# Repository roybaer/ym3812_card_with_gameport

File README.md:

# YM3812 card with gameport

This 8-bit ISA card is essentially a clone of Amstrad's Adlib clone with gameport.

The routing and silk screen are a bit tidier and the DA15 connector has been shifted to make it easier to adapt off-the-shelf slot brackets.

## Front view

This picture shows the front of the card.

## Vintage components

Besides readily available standard components, the card uses four vintage components:

- Yamaha YM3812 (OPL2 FM synthesizer)
- Yamaha Y3014B (matching DAC for OPL2)
- TDA7233 (amplifier)
- NE558 (quad timer IC)

## License

The following license applies to the files in this repository:

This work is licensed under the Creative Commons Attribution-ShareAlike 4.0 International License. To view a copy of this license, visit http://creativecommons.org/licenses/by-sa/4.0/ or send a letter to Creative Commons, PO Box 1866, Mountain View, CA 94042, USA.

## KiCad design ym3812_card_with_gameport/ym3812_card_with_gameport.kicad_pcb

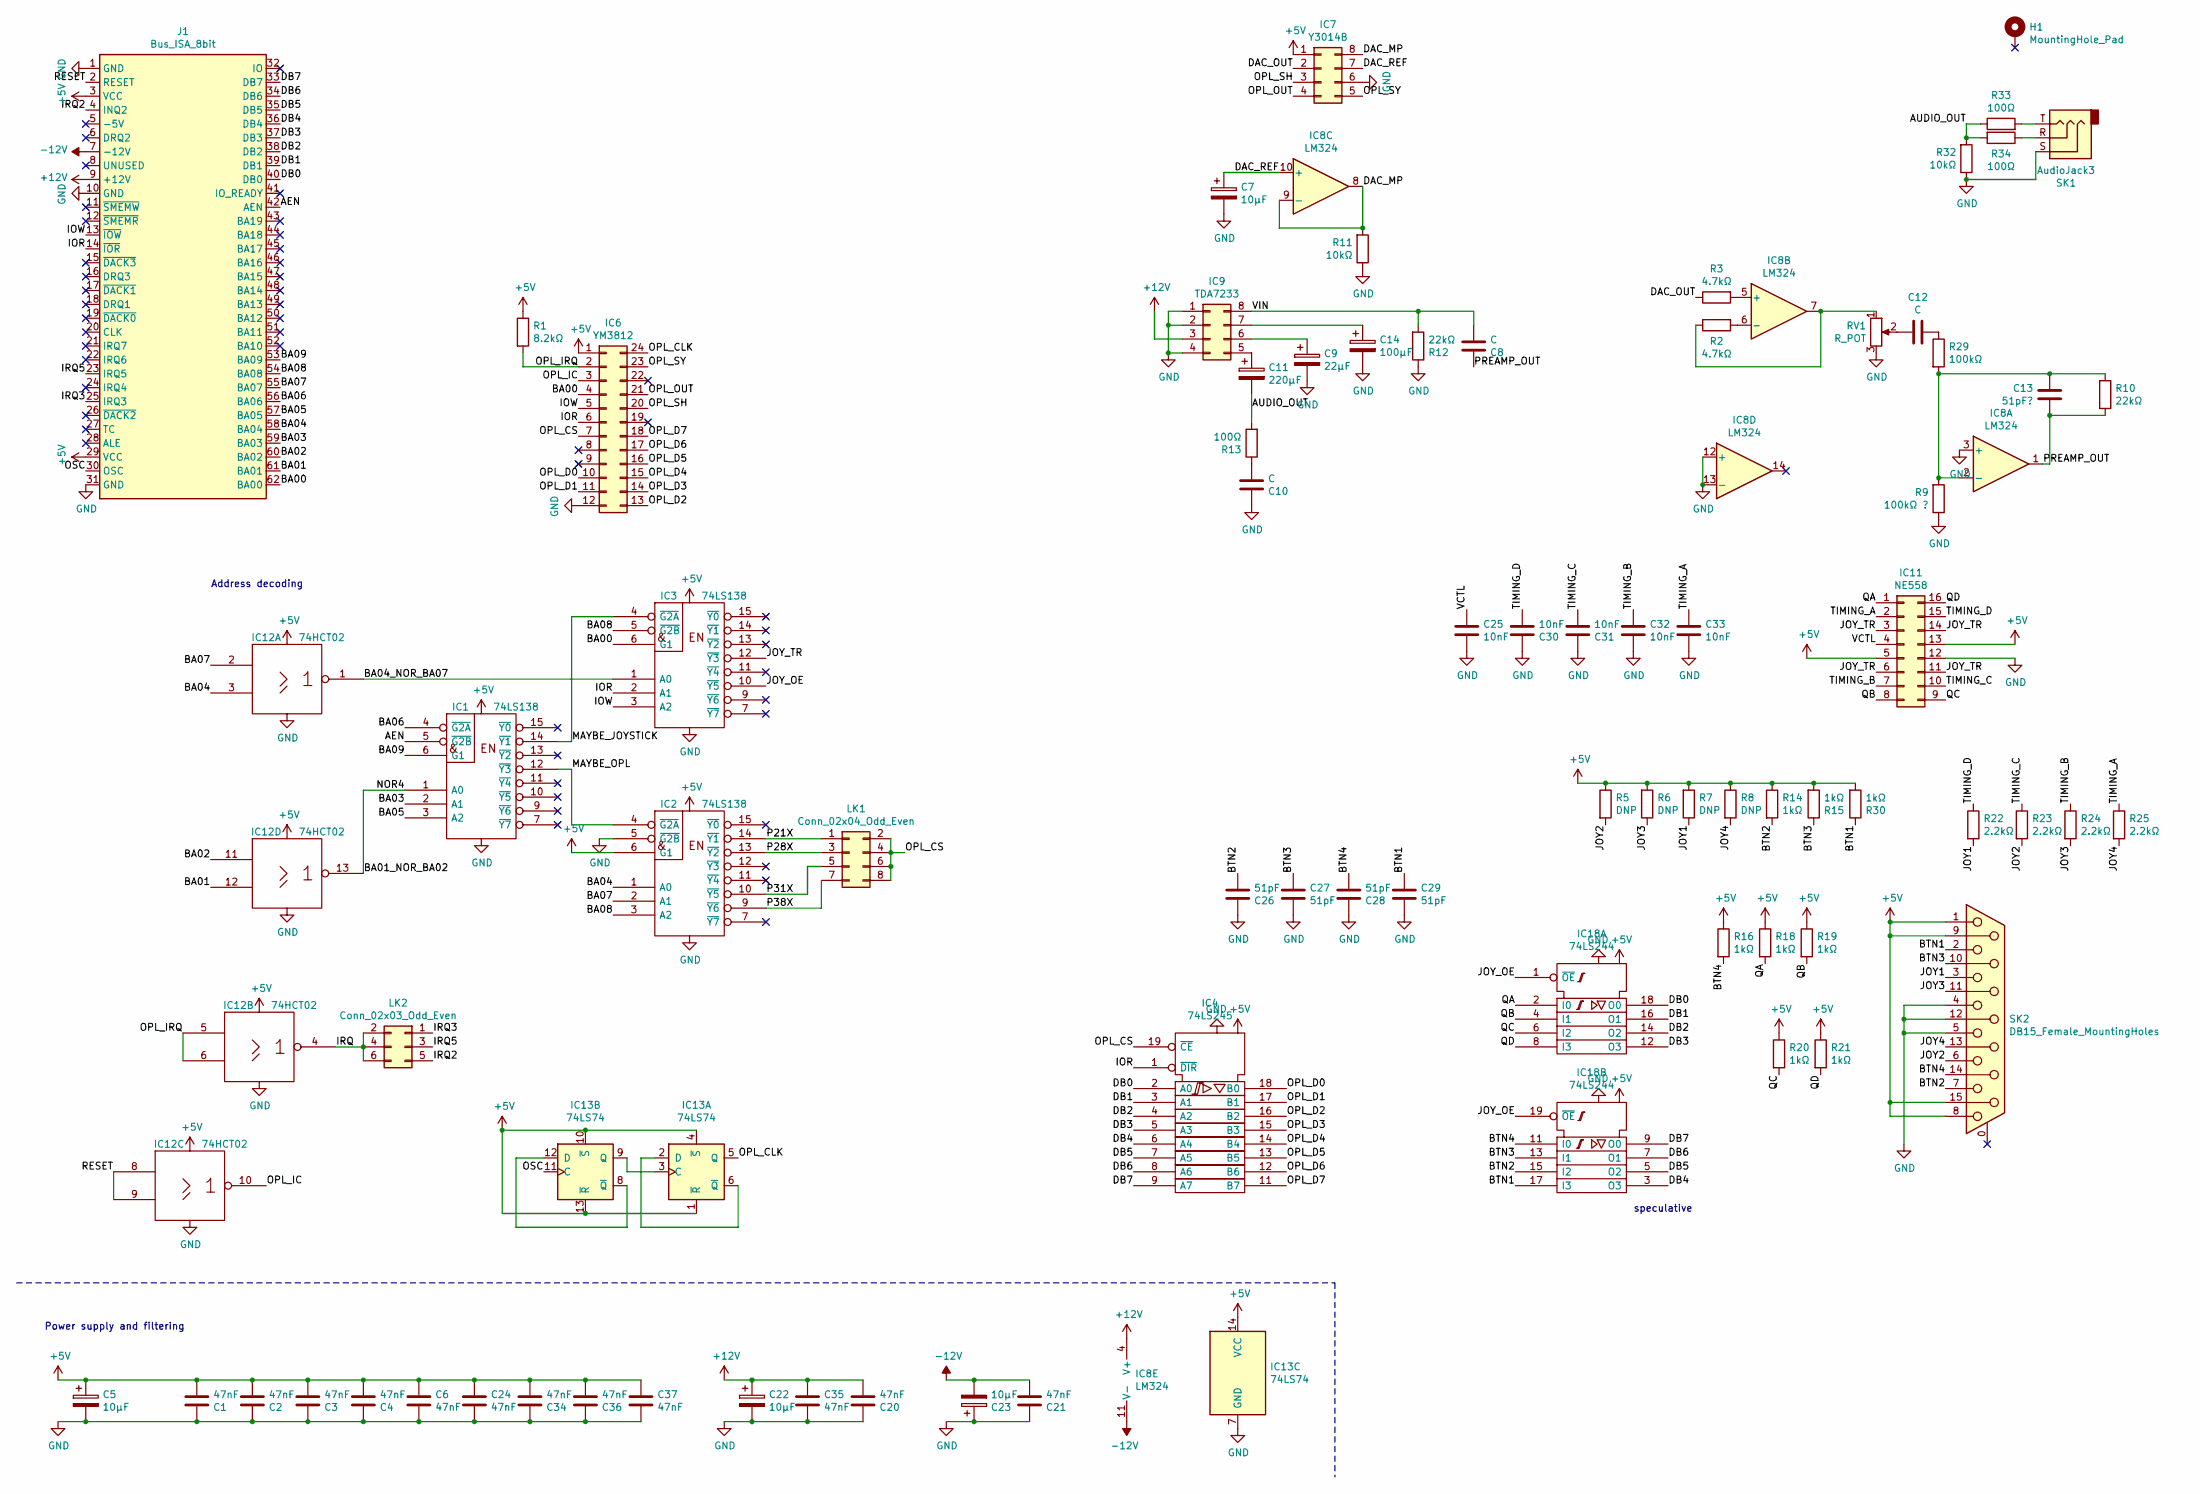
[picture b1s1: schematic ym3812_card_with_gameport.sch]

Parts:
C1, C2, C3, C4, C6, C20, C21, C24, C34, C35, C36, C37: 47nF; C_1206_3216Metric
C5, C7, C22, C23: 10µF; CP_Radial_D5.0mm_P2.50mm
C8, C10, C12: C; C_1206_3216Metric
C9: 22µF; CP_Radial_D5.0mm_P2.50mm
C11: 220µF; CP_Radial_D8.0mm_P5.00mm
C13: 51pF?; C_1206_3216Metric
C14: 100µF; CP_Radial_D6.3mm_P2.50mm
C25, C30, C31, C32, C33: 10nF; C_1206_3216Metric
C26, C27, C28, C29: 51pF; C_1206_3216Metric
H1: MountingHole_Pad; MountingHole_3.2mm_M3_Pad_Via
IC1, IC2, IC3: 74LS138; SOIC-16_3.9x9.9mm_P1.27mm
IC4: 74LS245; SOIC-20W_7.5x12.8mm_P1.27mm
IC6: YM3812; DIP-24_W15.24mm
IC7: Y3014B; DIP-8_W7.62mm
IC8: LM324; SOIC-14_3.9x8.7mm_P1.27mm
IC9: TDA7233; DIP-8_W7.62mm
IC11: NE558; SOIC-16W_7.5x10.3mm_P1.27mm
IC12: 74HCT02; SOIC-14_3.9x8.7mm_P1.27mm
IC13: 74LS74; SOIC-14_3.9x8.7mm_P1.27mm
IC18: 74LS244; SOIC-20W_7.5x12.8mm_P1.27mm
J1: Bus_ISA_8bit; BUS_AT
LK1: Conn_02x04_Odd_Even; PinHeader_2x04_P2.54mm_Vertical
LK2: Conn_02x03_Odd_Even; PinHeader_2x03_P2.54mm_Vertical
R1: 8.2kΩ; R_1206_3216Metric
R2, R3: 4.7kΩ; R_1206_3216Metric
R5, R6, R7, R8: DNP; R_1206_3216Metric
R9: 100kΩ ?; R_1206_3216Metric
R10, R12: 22kΩ; R_1206_3216Metric
R11, R32: 10kΩ; R_1206_3216Metric
R13, R33, R34: 100Ω; R_1206_3216Metric
R14, R15, R16, R18, R19, R20, R21, R30: 1kΩ; R_1206_3216Metric
R22, R23, R24, R25: 2.2kΩ; R_1206_3216Metric
R29: 100kΩ; R_1206_3216Metric
RV1: R_POT; Potentiometer_Alps_RK09K_Single_Horizontal
SK1: AudioJack3; Jack_3.5mm_CUI_SJ1-3525N_Horizontal
SK2: DB15_Female_MountingHoles; DSUB-15_Female_Horizontal_P2.77x2.84mm_EdgePinOffset7.70mm_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

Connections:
+5V: C1.2, C2.2, C3.2, C4.2, C5.1, C6.1, C24.1, C34.2, C36.2, C37.1, IC1.16 (VCC), IC2.6 (G1), IC2.16 (VCC), IC3.16 (VCC), IC4.20 (VCC), IC6.1, IC7.1, IC11.5, IC11.13, IC12.14 (VCC), IC13.1 (~R), IC13.4 (~S), IC13.10 (~S), IC13.13 (~R), IC13.14 (VCC), IC18.20 (VCC), J1.3 (VCC), J1.29 (VCC), R1.1, R5.1, R6.2, R7.2, R8.1, R14.1, R15.2, R16.1, R18.1, R19.1, R20.1, R21.1, R30.2, SK2.1, SK2.8, SK2.9, SK2.15
+12V: C20.2, C22.1, C35.1, IC8.4 (V+), IC9.3, J1.9 (+12V)
-12V: C21.2, C23.2, IC8.11 (V-), J1.7 (-12V)
/AEN: IC1.5 (~G2B), J1.42 (AEN)
/AUDIO_OUT: C11.2, R13.2, R32.2, R33.1, R34.2
/BA00: IC3.6 (G1), IC6.4, J1.62 (BA00)
/BA01: IC12.12, J1.61 (BA01)
/BA01_NOR_BA02: IC1.1 (A0), IC12.13
/BA02: IC12.11, J1.60 (BA02)
/BA03: IC1.2 (A1), J1.59 (BA03)
/BA04: IC2.1 (A0), IC12.3, J1.58 (BA04)
/BA04_NOR_BA07: IC3.1 (A0), IC12.1
/BA05: IC1.3 (A2), J1.57 (BA05)
/BA06: IC1.4 (~G2A), J1.56 (BA06)
/BA07: IC2.2 (A1), IC12.2, J1.55 (BA07)
/BA08: IC2.3 (A2), IC3.5 (~G2B), J1.54 (BA08)
/BA09: IC1.6 (G1), J1.53 (BA09)
/BTN1: C29.1, IC18.17 (I3), R30.1, SK2.2
/BTN2: C26.2, IC18.15 (I2), R14.2, SK2.7
/BTN3: C27.1, IC18.13 (I1), R15.1, SK2.10
/BTN4: C28.2, IC18.11 (I0), R16.2, SK2.14
/DAC_MP: IC7.8, IC8.8, IC8.9 (-), R11.2
/DAC_OUT: IC7.2, R3.1
/DAC_REF: C7.1, IC7.7, IC8.10 (+)
/DB0: IC4.2 (A0), IC18.18 (O0), J1.40 (DB0)
/DB1: IC4.3 (A1), IC18.16 (O1), J1.39 (DB1)
/DB2: IC4.4 (A2), IC18.14 (O2), J1.38 (DB2)
/DB3: IC4.5 (A3), IC18.12 (O3), J1.37 (DB3)
/DB4: IC4.6 (A4), IC18.3 (O3), J1.36 (DB4)
/DB5: IC4.7 (A5), IC18.5 (O2), J1.35 (DB5)
/DB6: IC4.8 (A6), IC18.7 (O1), J1.34 (DB6)
/DB7: IC4.9 (A7), IC18.9 (O0), J1.33 (DB7)
/IOR: IC3.2 (A1), IC4.1 (~DIR), IC6.6, J1.14 (~IOR)
/IOW: IC3.3 (A2), IC6.5, J1.13 (~IOW)
/IRQ: IC12.4, LK2.2, LK2.4, LK2.6
/IRQ2: J1.4 (INQ2), LK2.5
/IRQ3: J1.25 (IRQ3), LK2.1
/IRQ5: J1.23 (IRQ5), LK2.3
/JOY1: R7.1, R22.2, SK2.3
/JOY2: R5.2, R23.2, SK2.6
/JOY3: R6.1, R24.2, SK2.11 (P111)
/JOY4: R8.2, R25.2, SK2.13
/JOY_OE: IC3.10 (~Y5), IC18.1 (~OE), IC18.19 (~OE)
/JOY_TR: IC3.12 (~Y3), IC11.3, IC11.6, IC11.11, IC11.14
/MAYBE_JOYSTICK: IC1.14 (~Y1), IC3.4 (~G2A)
/MAYBE_OPL: IC1.12 (~Y3), IC2.4 (~G2A)
/OPL_CLK: IC6.24, IC13.5 (Q)
/OPL_CS: IC4.19 (~CE), IC6.7, LK1.2, LK1.4, LK1.6, LK1.8
/OPL_D0: IC4.18 (B0), IC6.10
/OPL_D1: IC4.17 (B1), IC6.11
/OPL_D2: IC4.16 (B2), IC6.13
/OPL_D3: IC4.15 (B3), IC6.14
/OPL_D4: IC4.14 (B4), IC6.15
/OPL_D5: IC4.13 (B5), IC6.16
/OPL_D6: IC4.12 (B6), IC6.17
/OPL_D7: IC4.11 (B7), IC6.18
/OPL_IC: IC6.3, IC12.10
/OPL_IRQ: IC6.2, IC12.5, IC12.6, R1.2
/OPL_OUT: IC6.21, IC7.4
/OPL_SH: IC6.20, IC7.3
/OPL_SY: IC6.23, IC7.5
/OSC: IC13.11 (C), J1.30 (OSC)
/P21X: IC2.14 (~Y1), LK1.1
/P28X: IC2.13 (~Y2), LK1.3
/P31X: IC2.10 (~Y5), LK1.5
/P38X: IC2.9 (~Y6), LK1.7
/PREAMP_OUT: C8.1, C13.1, IC8.1, R10.1
/QA: IC11.1, IC18.2 (I0), R18.2
/QB: IC11.8, IC18.4 (I1), R19.2
/QC: IC11.9, IC18.6 (I2), R20.2
/QD: IC11.16, IC18.8 (I3), R21.2
/RESET: IC12.8, IC12.9, J1.2 (RESET)
/TIMING_A: C33.1, IC11.2, R25.1
/TIMING_B: C32.1, IC11.7, R24.1
/TIMING_C: C31.2, IC11.10, R23.1
/TIMING_D: C30.2, IC11.15, R22.1
/VCTL: C25.1, IC11.4
/VIN: C8.2, IC9.8, R12.2
GND: C1.1, C2.1, C3.1, C4.1, C5.2, C6.2, C7.2, C9.2, C10.1, C14.2, C20.1, C21.1, C22.2, C23.1, C24.2, C25.2, C26.1, C27.2, C28.1, C29.2, C30.1, C31.1, C32.2, C33.2, C34.1, C35.2, C36.1, C37.2, IC1.8 (GND), IC2.5 (~G2B), IC2.8 (GND), IC3.8 (GND), IC4.10 (GND), IC6.12, IC7.6, IC8.3 (+), IC8.12 (+), IC8.13 (-), IC9.1, IC9.2, IC9.4, IC11.12, IC12.7 (GND), IC13.7 (GND), IC18.10 (GND), J1.1 (GND), J1.10 (GND), J1.31 (GND), R9.1, R11.1, R12.1, R32.1, RV1.3, SK1.S, SK2.4, SK2.5, SK2.12
unnamed: C9.1, IC9.6
unnamed: C10.2, R13.1
unnamed: C11.1, IC9.5
unnamed: C12.1, RV1.2
unnamed: C12.2, R29.1
unnamed: C13.2, IC8.2 (-), R9.2, R10.2, R29.2
unnamed: C14.1, IC9.7
unnamed: IC8.5 (+), R3.2
unnamed: IC8.6 (-), R2.2
unnamed: IC8.7, R2.1, RV1.1
unnamed: IC13.2 (D), IC13.6 (~Q)
unnamed: IC13.3 (C), IC13.9 (Q)
unnamed: IC13.8 (~Q), IC13.12 (D)
unnamed: R33.2, SK1.T
unnamed: R34.1, SK1.R

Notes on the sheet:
speculative
Power supply and filtering
Address decoding

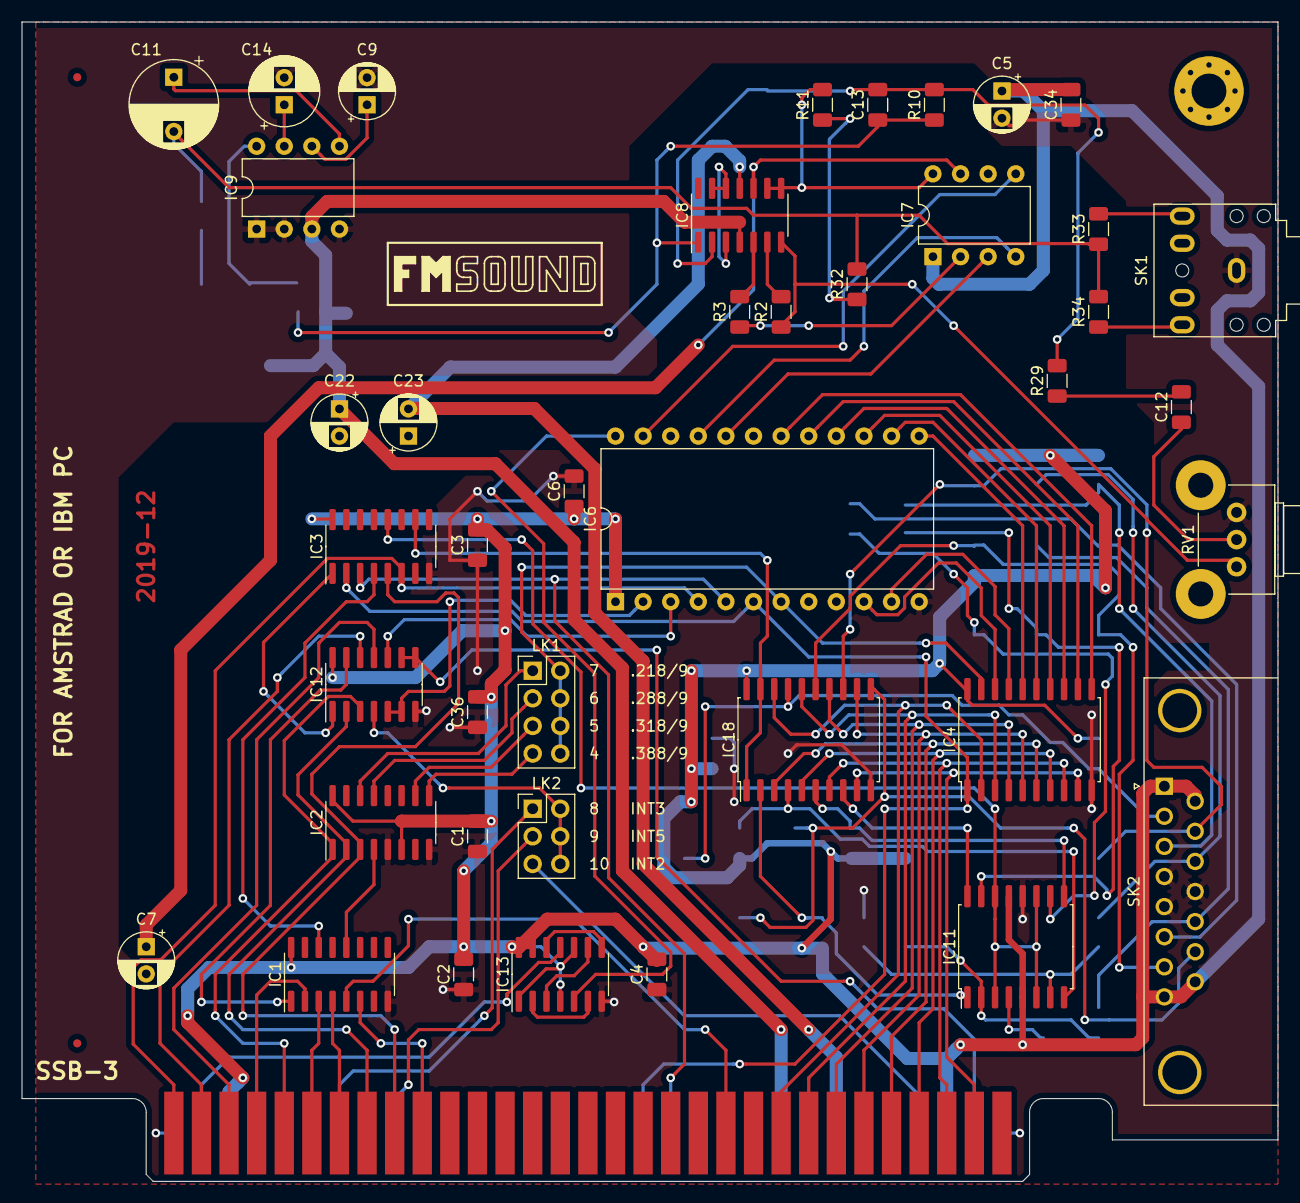
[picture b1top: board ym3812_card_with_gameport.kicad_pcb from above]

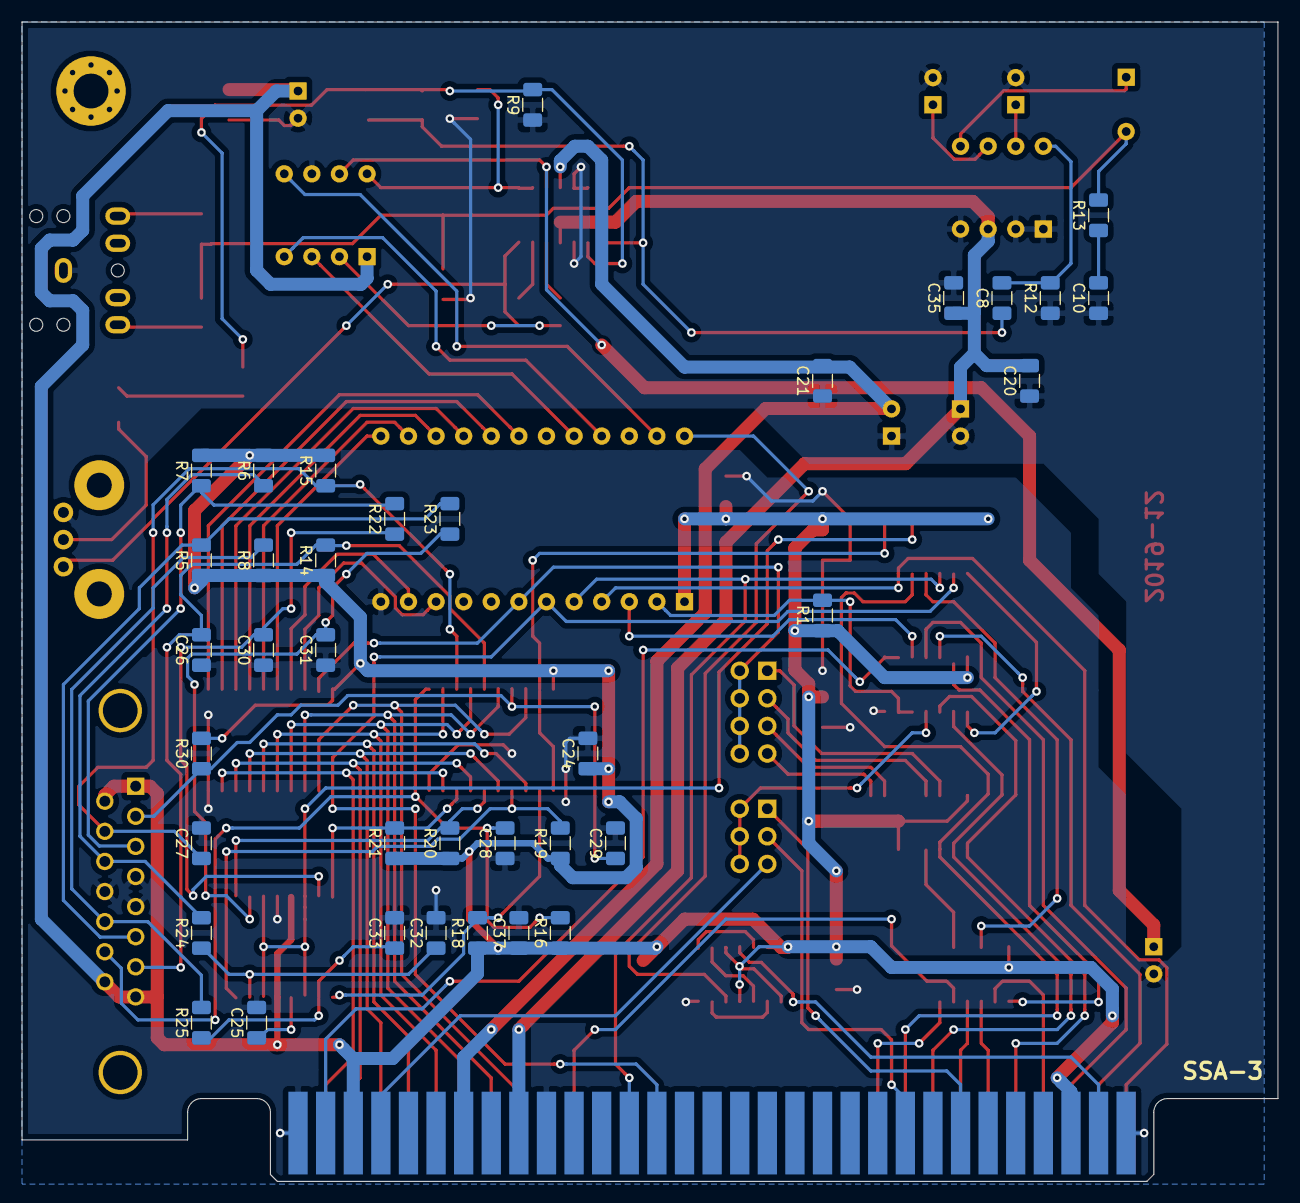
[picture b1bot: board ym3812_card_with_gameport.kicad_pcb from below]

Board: 2 copper layers, 115.6 x 106.7 mm, 79 parts (36 on the bottom side), 94 nets.

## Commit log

2019-10-29 some corrections, GND and VCC
2019-11-17 mostly complete schematic
2019-11-28 more accurate component positions
2019-12-06 corrections and some new traces
2019-12-23 minor corrections, routing complete
2019-12-23 layout beautification
2019-12-23 adapt to Keystone bracket 9200-3
2019-12-24 adjust edge connector
2019-12-24 mark R5, R6, R7 and R8 as DNP
2019-12-24 add README.md with picture
